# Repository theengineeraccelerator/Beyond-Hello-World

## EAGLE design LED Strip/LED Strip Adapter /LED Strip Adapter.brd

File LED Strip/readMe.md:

The following files make up this demo

.csv file: Chase, ColorWipe, Arbitrary Animation - These are CSV files that allow you to define the animation in time as if it was a bit map. Column represents a LED and each row represents one frame. Chase and ColorWipe recreate some of the effects in the strandtest demo and Arbitratry Animation shows a custom animation for the strip.The table uses 33 columns: 32 for each LED and the 33rd to add a comma at the end of each row. This means the table will match the code syntax with no changes

Frame_Table_Animation.ino - This is the demo code that uses a non-blocking timer to display each frame. 

Frame_Table.h - This contains the frame table derived from the .csv files. You also define the colors and frames per second in this file

LED Strip Adapter - These are the Eagle files for the adapter board that connects the strip to the external power supply and the Arduino

Neopixel Demo BOM - This contains all the parts I used to create the demo. 

Usage: 
	- Define the colors you want to use and update or add them to the Frame_Table.h. Be sure to use the 565RGB format. To convert 888RGB to 565RGB you can used http://www.rinkydinkelectronics.com/calc_rgb565.php 
	- Open the .csv in a spreadsheet editor and adjust the color locations as needed and save again
	- Open the same .csv in a text editor and copy the whole file
	- In Frame_Table.h select all the hex in the PixelData array and replace it with the hex values you copied. 
	- Save and upload to the Arduino.

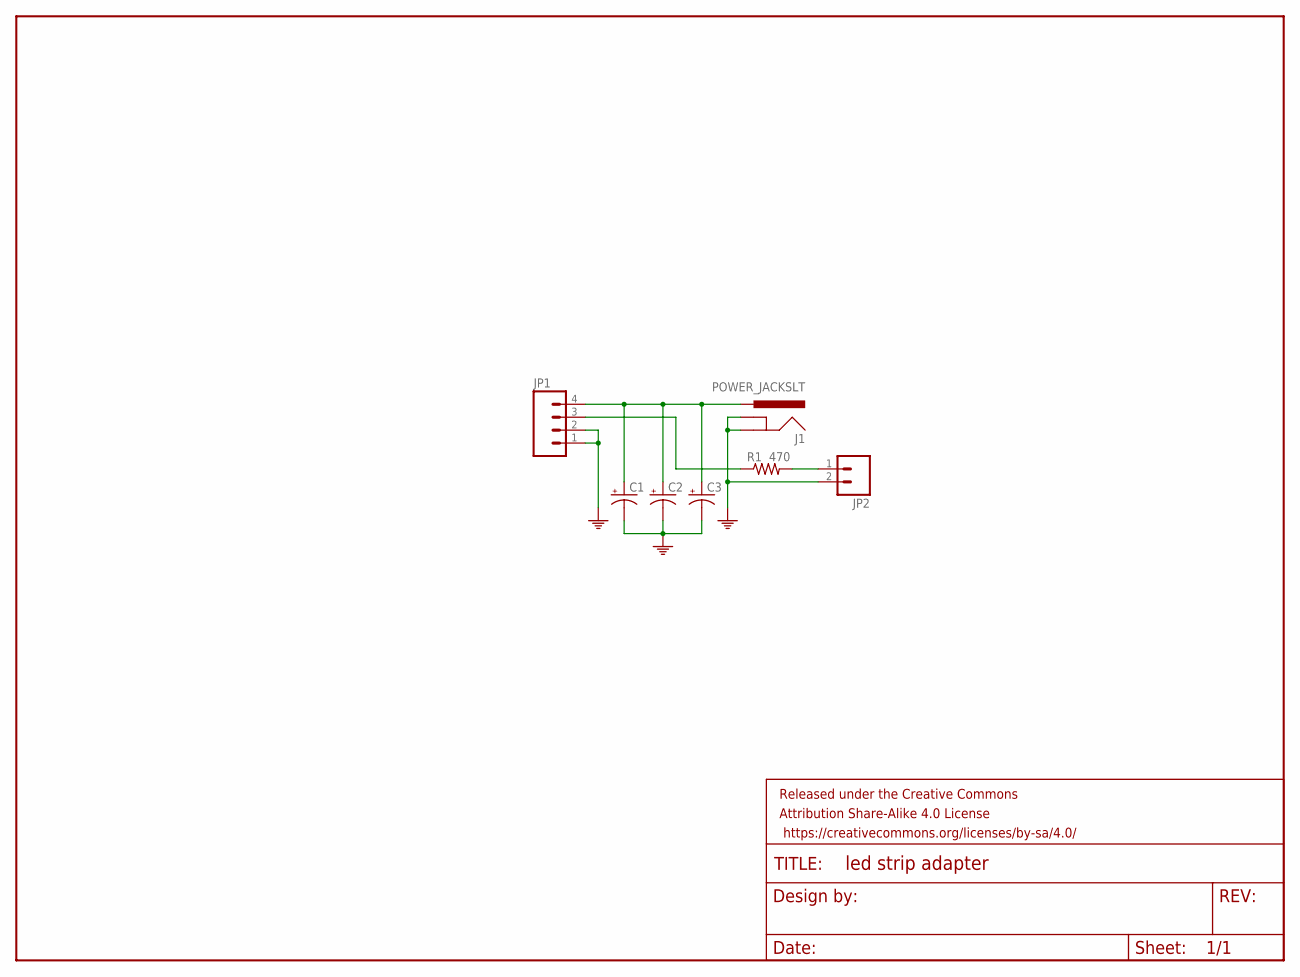
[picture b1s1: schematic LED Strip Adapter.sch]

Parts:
C1, C2, C3: CAP_POLPTH2; CPOL-RADIAL-10UF-25V
FRAME1: FRAME-LETTER; CREATIVE_COMMONS
J1: POWER_JACKSLT; POWER_JACK_SLOT
JP1: M04LOCK_LONGPADS; 1X04_LOCK_LONGPADS
JP2: M02LOCK_LONGPADS; 1X02_LOCK_LONGPADS
R1: 470; 1206

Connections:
GND: C1.2 (-), C2.2 (-), C3.2 (-), J1.GND@1 (GNDBREAK), J1.GND@2 (GND), JP1.1, JP1.2, JP2.2
unnamed: JP2.1, R1.2
PWR: C1.1 (+), C2.1 (+), C3.1 (+), J1.PWR, JP1.4
SIG: JP1.3, R1.1

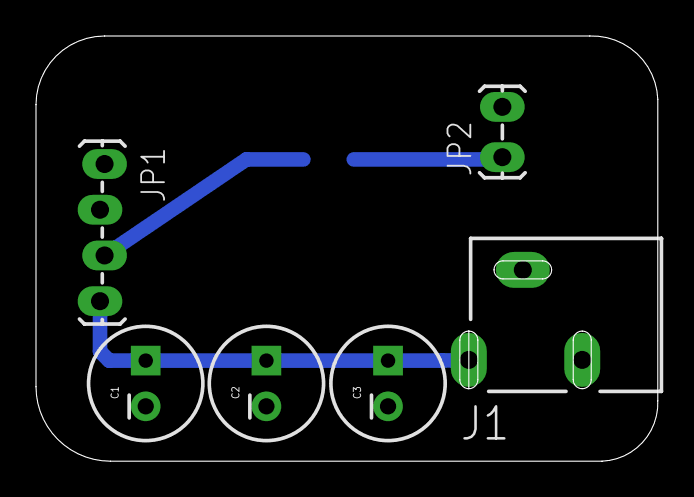
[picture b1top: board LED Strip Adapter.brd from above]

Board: 2 copper layers, 34.5 x 23.6 mm, 8 parts (1 on the bottom side), 4 nets.

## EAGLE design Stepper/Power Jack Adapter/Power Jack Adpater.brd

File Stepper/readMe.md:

The following files make up this demo

SparkFun_Easy_Driver_Basic_Demo.ino - This is the test code for the Easy Driver I used to make sure that the hardware was connected up correctly

AccelStepper_Minimum.ino - This is the minimum amount of code that I found the could run the stepper reasonably. The setAcceleration and setMaxSpeed were required to get the motor to run at a resonable speed.

Bounce_BHWE.ino - This is adapted from one of the AccelStepper library examples to work with the setup that I had. 

Power Jack Adapter - These are the eagle files created to make the barrel jack to EasyDriver adapter board. The board was cut on an Othermill.  

AccelStepper Demo BOM.xlsx - This contains all the parts I used to create the demo.

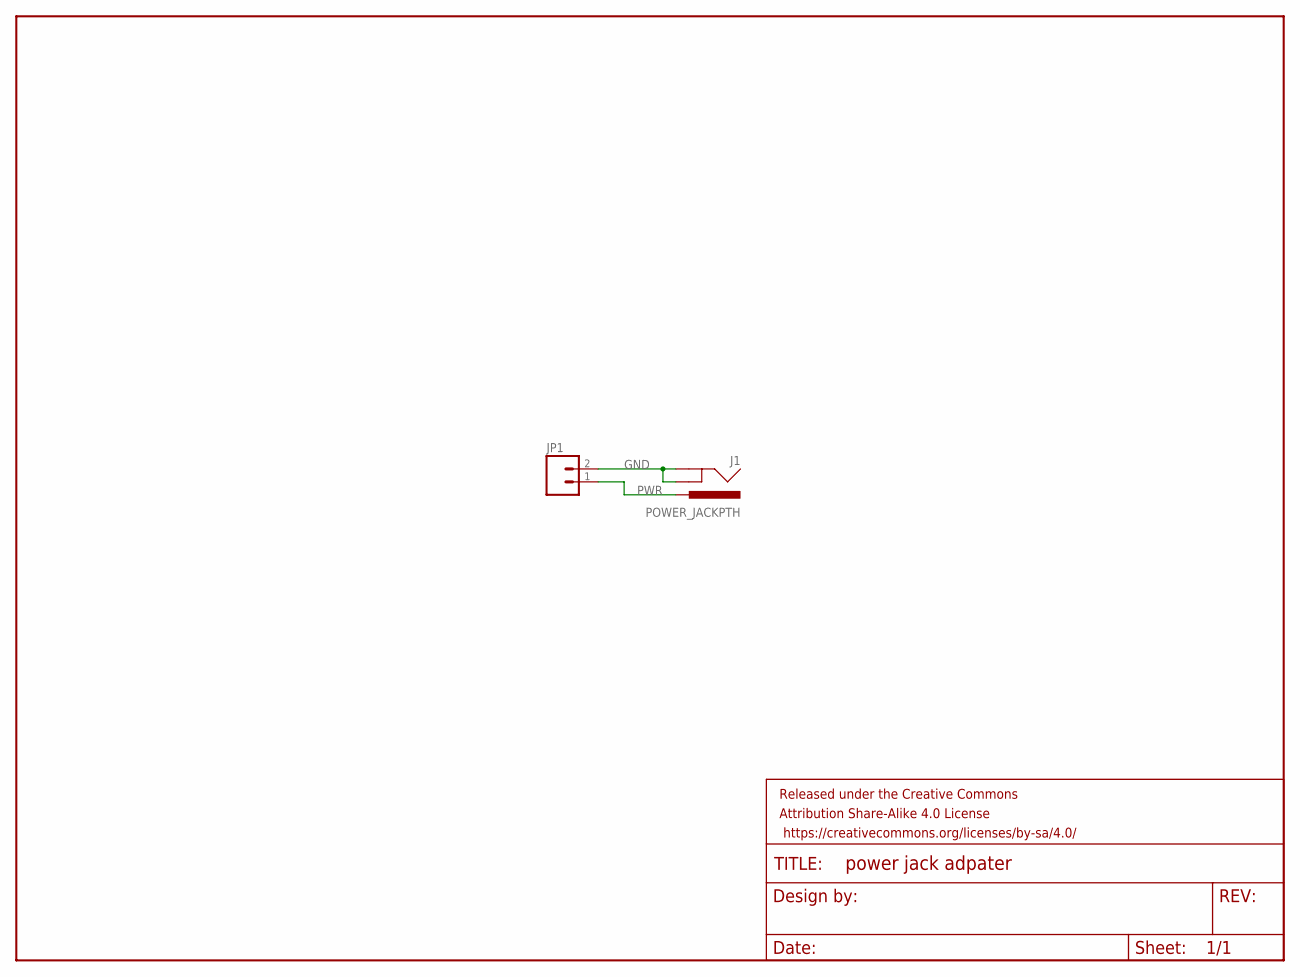
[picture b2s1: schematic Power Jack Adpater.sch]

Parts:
FRAME1: FRAME-LETTER; CREATIVE_COMMONS
J1: POWER_JACKPTH; POWER_JACK_PTH
JP1: M02LOCK_LONGPADS; 1X02_LOCK_LONGPADS

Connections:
GND: J1.GND, J1.GNDBREAK, JP1.2
PWR: J1.PWR, JP1.1

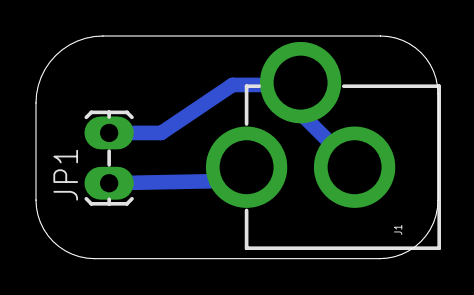
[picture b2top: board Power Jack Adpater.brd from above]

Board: 2 copper layers, 22.3 x 12.4 mm, 3 parts (0 on the bottom side), 2 nets.

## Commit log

2017-02-24 Stepper Demo
2017-03-11 Added LED strip adapter pub
2017-03-31 Updated Stepper Readme and initial upload of Neopixel Demo
2017-05-11 Authenticator Demo Upload
2017-05-16 Added Rotary Breakout Board to Non Blocking Timer folder

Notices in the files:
parts and their libraries:
1-Generic: Released under the Creative Commons Attribution Share-Alike 4.0 License
1-Generic: https://creativecommons.org/licenses/by-sa/4.0
1-Generic: Released under the Creative Commons
